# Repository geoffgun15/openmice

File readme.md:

# OpenMice

Custom PAW3395 rechargeable mouse, USB wireless receiver, and browser configurator.

Standalone repository: https://github.com/geoffgun15/openmice.
Migrated from the original fork with all eight commits retained and the
confidential PixArt PDF removed from every commit. Historical commit IDs changed.

**A1 is a routed prototype package.** Both boards pass KiCad electrical,
clearance, connectivity and schematic parity checks. Custom runtime and
bootloader builds, factory HEX, runtime UF2 and fabrication exports are included.
**Physical tests are NOT RUN: there is no assembled board.** Review the
[first-article procedure](docs/FIRST_ARTICLE.md) and
[fabrication requirements](docs/FABRICATION.md) before a prototype order.

| Component | Included |
|---|---|
| Mouse | Bare PAW3395, nRF52840 module, 1S LiPo charger/power path, five buttons + scroll |
| Receiver | Custom nRF52840 board, USB-C, BLE-to-USB HID and configuration bridge |
| Firmware | Corrected sensor startup/ID/timing, 16-bit motion, DPI, bindings, persistence |
| Editor | Web Serial, DPI, mouse/keyboard bindings, Apply/Save, import/export and demo |

The radio modules are soldered components on custom PCBs; nice!nano is no longer
used. BLE is the prototype radio; proprietary 1000 Hz wireless is not implemented.

- [Hardware files and validation status](hardware/README.md)
- [Setup, protocol and verification](docs/SETUP.md)
- [Mouse schematic](hardware/mouse/mouse.kicad_sch) / [PCB](hardware/mouse/mouse.kicad_pcb)
- [Receiver schematic](hardware/receiver/receiver.kicad_sch) / [PCB](hardware/receiver/receiver.kicad_pcb)
- [Browser editor](web/index.html)

## Board renders

KiCad assembly renders with all 51 mouse and 18 receiver components fitted.
The sensor, radio module, USB-C, charger and crystal use simplified visual models;
these images do not validate mechanical fit. The battery, main click switches
and scroll encoder connect externally. See [model details](hardware/libraries/3dmodels/README.md).

| Mouse PCB · 64 × 94 mm | Wireless receiver PCB · 28 × 54 mm |
|---|---|
|  |  |

Bare PCB views: [mouse](output/hardware/mouse/board-3d.png) ·
[receiver](output/hardware/receiver/board-3d.png).

## Preview

```sh
python -m http.server 8765 --bind 127.0.0.1 --directory web
```

Open http://127.0.0.1:8765/ in desktop Chrome/Edge. Demo mode works without hardware.
A real connection requires the supplied runtime and mouse/receiver.

Native build details, hashes and CAD export workflow: [BUILD.md](docs/BUILD.md).

## Development

```sh
python -m unittest discover -s tests -v
node --test web/test.mjs
python tools/package_firmware.py
```

`tools/build_hardware.py` regenerates starting placements and overwrites manual edits.
The confidential sensor PDF is excluded from this public repository and its Git history.
Prototype assumptions: LM19-LSI optics,
64 x 94 mm mouse outline, external switch/encoder contacts, and a protected
300 mAh cell with compatible NTC temperature sensing.

Project code: MIT. Vendored KiCad libraries retain their upstream licenses;
see hardware/README.md. Obtain sensor documentation through an authorized source.

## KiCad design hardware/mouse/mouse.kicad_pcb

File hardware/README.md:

# Hardware A1: routed prototype candidates

Both custom boards are routed and have zero findings in KiCad 10.0.6 ERC,
DRC, connectivity and schematic parity checks. Manufacturing exports are in
`output/hardware/` and fabrication ZIPs in `output/`. **Physical tests are NOT RUN.**

| Board | Outline | Components | Functional nets |
|---|---|---:|---:|
| Mouse | 64 × 94 mm | 51 | 39 |
| USB-C receiver | 28 × 54 mm | 18 | 13 |

Both boards use soldered Raytac MDBT50Q-1MV2 nRF52840 modules. The mouse has a
bare PAW3395DM-T6QU, 1.9 V sensor/LED rail, 3.0 V MCU/VDDIO rail, external contact
headers for five switches and a scroll encoder, USB-C, SWD and Pair/reset buttons.
The receiver connects by USB-C cable and bridges BLE input/configuration to USB.
Proprietary 1000 Hz wireless is not implemented.

BQ24072 provides charging and system power path for a protected 1S 3.7 V nominal
300 mAh LiPo pack with thermally attached compatible 10k NTC (J3 BAT+, GND, NTC).
USB100 mode caps total input at 100 mA; R_ISET 5.90k programs about 151 mA before
input/system limits, R_ILIM 3.09k is overridden, R_TMR 68k is about 9.1 hours nominal.
The switch is downstream of charging. Firmware battery telemetry is approximate;
pack protection handles over-discharge. USB suspend management is not implemented.

Sensor VDDREG is decoupled only. TLV70019 supplies sensor VDD/LED (5.6 ohm 1%
resistor); TLV70030 supplies VDDIO and MCU VDD/VDDH. DCCH is unconnected. Separate
5.1k CC resistors and USBLC6-2SC6 protect USB; no PD. External 32.768 kHz crystal
loading needs bench verification. The module includes its normal-mode DC/DC parts.

Four layers use outer signal routing and two solid inner GND reference planes,
all-layer antenna keep-outs, routed optical/mounting apertures and charger thermal
vias. USB routing is manually protected. Review the
[fabrication specification](../docs/FABRICATION.md) for stack-up, impedance, filled thermal vias, lens and BOM
requirements before a first-article order. No shell or optical fit validation exists.

Editable native schematics/boards, local libraries, routing DSN/SES, BOM, placement
CSV and CAD-check reports are included. Regeneration overwrites routing; see
[build workflow](../docs/BUILD.md). The unused MouseSwitch_D2F_DRAFT footprint is
not in either BOM and is not validated. Bench bring-up is in
[FIRST_ARTICLE.md](../docs/FIRST_ARTICLE.md).

## References and licenses

- PAW3395DM-T6QU datasheet v1.3 (8 Apr 2024): confidential reference, excluded
  from this public repository; obtain through an authorized source.
- [Raytac module datasheet](https://www.raytac.com/tw/download/index.php?index_id=24).
- [BQ2407x datasheet, including BQ24072](https://www.ti.com/lit/ds/symlink/bq24074.pdf).
- [TLV700 regulators](https://www.ti.com/product/TLV700).
- [KiCad footprints](https://github.com/KiCad/kicad-footprints) and
  [symbols](https://github.com/KiCad/kicad-symbols).

Vendored KiCad data retains upstream CC-BY-SA 4.0 licensing with the KiCad library
exception; see the [library license](https://www.kicad.org/libraries/license/).
Project code uses MIT. The confidential PixArt reference is not distributed.

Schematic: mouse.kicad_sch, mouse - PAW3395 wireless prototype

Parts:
C1, C5, C8: 1uF 10V X7R; C_0603_1608Metric
C2: 4.7uF 6.3V X5R; C_0603_1608Metric
C3, C4: 100nF 10V X7R; C_0603_1608Metric
C6, C7: 18pF C0G (tune); C_0603_1608Metric
C9, C17, C18: 10uF 6.3V X5R; C_0805_2012Metric
C10, C12, C14, C19: 100nF X7R; C_0603_1608Metric
C11: 4.7uF X5R; C_0603_1608Metric
C13: 10uF X5R; C_0805_2012Metric
C15: 33uF 6.3V X5R; C_0805_2012Metric
C16: 1uF 10V X7R; C_0805_2012Metric
J1: USB-C HRO TYPE-C-31-M-12; USB_C
J2: SWD: VDD / SWDIO / SWDCLK / GND / RESET; PinHeader_1x05_P2.54mm_Vertical
J3: Protected 1S 300mAh + 10k NTC (BAT/GND/NTC); JST_PH_B3B-PH-K_1x03_P2.00mm_Vertical
J4: Charger status: GND / PGOOD / CHG; PinHeader_1x03_P2.54mm_Vertical
J5: BUTTON_LEFT contact; PinHeader_1x02_P2.54mm_Vertical
J6: BUTTON_RIGHT contact; PinHeader_1x02_P2.54mm_Vertical
J7: BUTTON_MIDDLE contact; PinHeader_1x02_P2.54mm_Vertical
J8: BUTTON_BACK contact; PinHeader_1x02_P2.54mm_Vertical
J9: BUTTON_FORWARD contact; PinHeader_1x02_P2.54mm_Vertical
J10: Encoder: A / GND / B; PinHeader_1x03_P2.54mm_Vertical
R1, R2: 5.1k 1%; R_0603_1608Metric
R3, R5: 10k; R_0603_1608Metric
R4: 5.6R 1%; R_0603_1608Metric
R6: 5.90k 1%; R_0603_1608Metric
R7: 3.09k 1%; R_0603_1608Metric
R8: 68k 1%; R_0603_1608Metric
R9, R10: 100k 1%; R_0603_1608Metric
R11, R12: 100k; R_0603_1608Metric
SW1: PAIR TL3342; SW_SPST_TL3342
SW2: RESET TL3342; SW_SPST_TL3342
SW3: Power PCM12; SW_SPDT_PCM12
U1: MDBT50Q-1MV2; Raytac_MDBT50Q
U2: USBLC6-2SC6; SOT-23-6
U3: TLV70030DDCR; SOT-23-5
U4: PAW3395DM-T6QU; PAW3395DM_T6QU
U5: TLV70019DDCR; SOT-23-5
U6: BQ24072RGTR; BQ24072_RGT0016C
Y1: 32.768kHz 12.5pF ABS07; Crystal_SMD_3215-2Pin_3.2x1.5mm

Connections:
/BATTERY: C18.1, J3.1, R9.1, U6.2 (BAT), U6.3 (BAT)
/BATTERY_ADC: C19.1, R9.2, R10.1, U1.20 (P0.04/AIN2)
/BATTERY_NTC: J3.3, U6.1 (TS)
/BUTTON_BACK: J8.1, U1.46 (P0.22)
/BUTTON_FORWARD: J9.1, U1.48 (P0.24)
/BUTTON_LEFT: J5.1, U1.44 (P0.20)
/BUTTON_MIDDLE: J7.1, U1.45 (P0.23)
/BUTTON_RIGHT: J6.1, U1.43 (P0.21)
/CC1: J1.A5, R1.1
/CC2: J1.B5, R2.1
/CHARGER_ILIM: R7.1, U6.12 (ILIM)
/CHARGER_ISET: R6.1, U6.16 (ISET)
/CHARGER_TMR: R8.1, U6.14 (TMR)
/CHARGING: J4.3, R12.2, U6.9 (CHG)
/ENCODER_A: J10.1, U1.49 (P0.25)
/ENCODER_B: J10.3, U1.19 (P0.26)
/GND: C1.2, C2.2, C3.2, C4.2, C5.2, C6.2, C7.2, C8.2, C9.2, C10.2, C11.2, C12.2, C13.2, C14.2, C15.2, C16.2, C17.2, C18.2, C19.2, J1.A1, J1.A12, J1.B1, J1.B12, J1.S1, J2.4, J3.2, J4.1, J5.2, J6.2, J7.2, J8.2, J9.2, J10.2, R1.2, R2.2, R6.2, R7.2, R8.2, R10.2, SW1.2, SW2.2, U1.1 (GND), U1.2 (GND), U1.15 (GND), U1.33 (GND), U1.55 (GND), U2.2, U3.2, U4.3 (GND), U4.8 (GNDIO), U5.2, U6.4 (CE), U6.5 (EN2), U6.6 (EN1), U6.8 (VSS), U6.15 (TD), U6.17 (EP)
/LF_XL1: C6.1, U1.17 (XL1/P0.00), Y1.1
/LF_XL2: C7.1, U1.18 (XL2/P0.01), Y1.2
/MCU_RESET: J2.5, R3.2, SW2.1, U1.40 (~RESET~/P0.18)
/PAIR: SW1.1, U1.16 (P0.27)
/POWER_GOOD: J4.2, R11.2, U6.7 (PGOOD)
/SENSOR_IRQ: U1.27 (TRACEDATA2/P0.11), U4.9 (MOTION)
/SENSOR_LED_P: R4.2, U4.15 (LED_P)
/SENSOR_NCS: U1.38 (P0.16), U4.13 (NCS)
/SENSOR_RESET: U1.41 (P0.17), U4.14 (NRESET)
/SENSOR_VDDREG: C11.1, C12.1, U4.5 (VDDREG)
/SPI_MISO: R5.2, U1.39 (P0.15), U4.12 (MISO)
/SPI_MOSI: U1.37 (P0.13), U4.11 (MOSI)
/SPI_SCLK: U1.36 (P0.14), U4.10 (SCLK)
/SWDCLK: J2.3, U1.53 (SWDCLK)
/SWDIO: J2.2, U1.51 (SWDIO)
/SYSTEM: C17.1, SW3.1, U6.10 (OUT), U6.11 (OUT)
/SYSTEM_ON: C1.1, SW3.2, U3.1, U3.3
/USB_DM: J1.A7, J1.B7, U1.34 (D-), U2.3, U2.4
/USB_DP: J1.A6, J1.B6, U1.35 (D+), U2.1, U2.6
/USB_VBUS: C5.1, C16.1, J1.A4, J1.A9, J1.B4, J1.B9, U1.32 (VBUS), U2.5, U6.13 (IN)
/VDD_1V9: C9.1, C10.1, C15.1, R4.1, U4.4 (VDD), U5.5
/VDD_3V0: C2.1, C3.1, C4.1, C8.1, C13.1, C14.1, J2.1, R3.1, R5.1, R11.1, R12.1, U1.28 (VDD), U1.30 (VDDH), U3.5, U4.7 (VDDIO), U5.1, U5.3

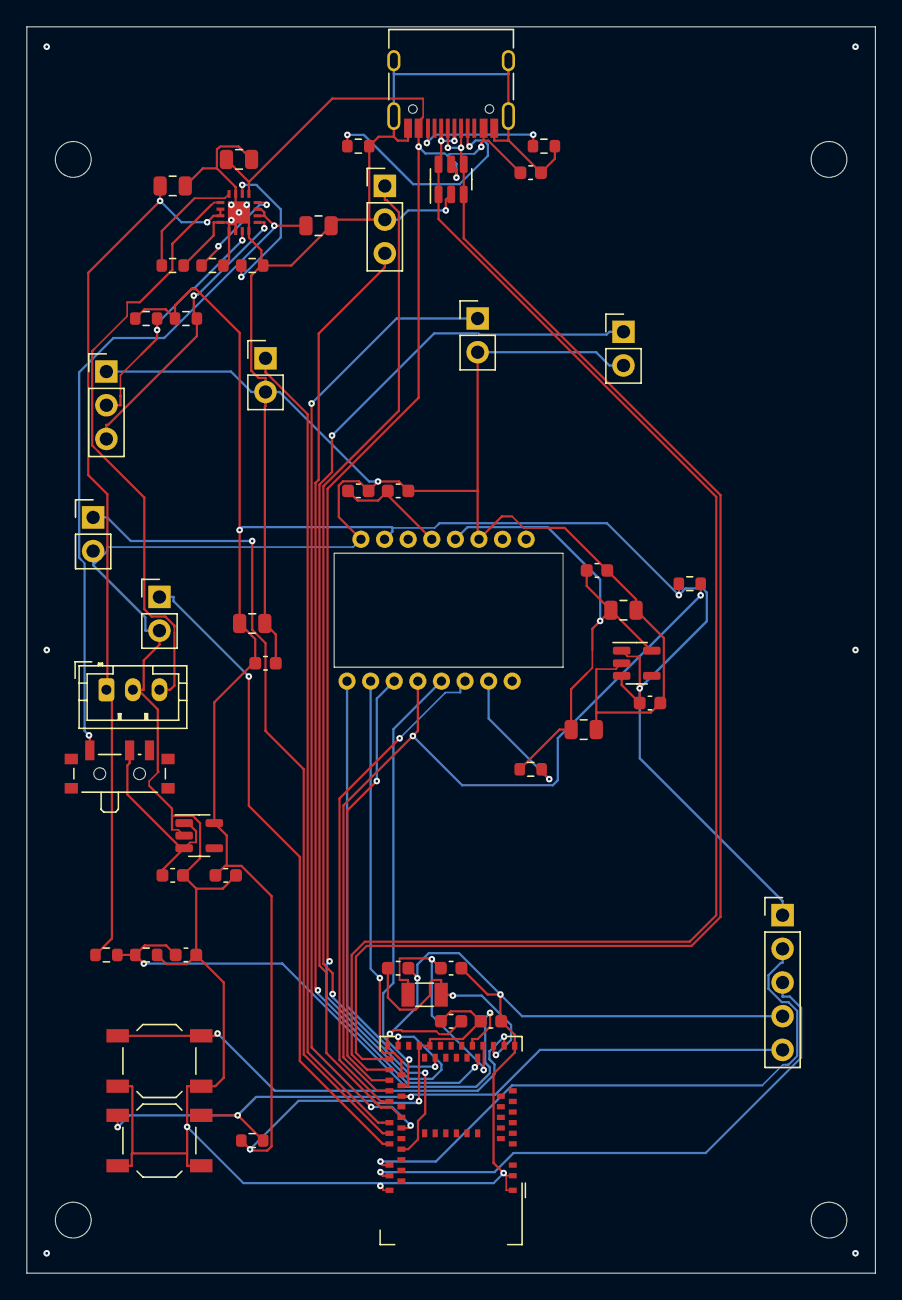
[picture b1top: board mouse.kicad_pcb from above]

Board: 4 copper layers, 64.0 x 94.0 mm, 51 parts (0 on the bottom side), 39 nets.

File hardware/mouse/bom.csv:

Reference,Value / part,Footprint,X mm,Y mm,Block
U1,MDBT50Q-1MV2,Raytac_MDBT50Q,32,84,controller
J1,USB-C HRO TYPE-C-31-M-12,USB_C,32,3.6,USB
U2,USBLC6-2SC6,SOT-23-6,38,7.6,USB
R1,5.1k 1%,R_0603_1608Metric,26,7.6,USB
R2,5.1k 1%,R_0603_1608Metric,29,7.6,USB
U3,TLV70030DDCR,SOT-23-5,13,61,power
C1,1uF 10V X7R,C_0603_1608Metric,11,64,power
C2,4.7uF 6.3V X5R,C_0603_1608Metric,15,64,power
C3,100nF 10V X7R,C_0603_1608Metric,32,75,controller
C4,100nF 10V X7R,C_0603_1608Metric,35,75,controller
C5,1uF 10V X7R,C_0603_1608Metric,35,10.6,USB
Y1,32.768kHz 12.5pF ABS07,Crystal_SMD_3215-2Pin_3.2x1.5mm,30,73,controller
C6,18pF C0G (tune),C_0603_1608Metric,28,71,controller
C7,18pF C0G (tune),C_0603_1608Metric,32,71,controller
J2,SWD: VDD / SWDIO / SWDCLK / GND / RESET,PinHeader_1x05_P2.54mm_Vertical,57,67,debug
SW1,PAIR TL3342,SW_SPST_TL3342,10,78,controls
SW2,RESET TL3342,SW_SPST_TL3342,10,84,controls
R3,10k,R_0603_1608Metric,14,84,controller
U4,PAW3395DM-T6QU,PAW3395DM_T6QU,32,44,sensor
U5,TLV70019DDCR,SOT-23-5,46,48,sensor
C8,1uF 10V X7R,C_0603_1608Metric,47,51,sensor
C9,10uF 6.3V X5R,C_0805_2012Metric,45,44,sensor
C10,100nF X7R,C_0603_1608Metric,43,41,sensor
C11,4.7uF X5R,C_0603_1608Metric,25,35,sensor
C12,100nF X7R,C_0603_1608Metric,28,35,sensor
C13,10uF X5R,C_0805_2012Metric,17,45,sensor
C14,100nF X7R,C_0603_1608Metric,18,48,sensor
C15,33uF 6.3V X5R,C_0805_2012Metric,42,53,sensor
R4,5.6R 1%,R_0603_1608Metric,40,52,sensor
R5,10k,R_0603_1608Metric,50,42,sensor
U6,BQ24072RGTR,VQFN-16-1EP_3x3mm_P0.5mm_EP1.45x1.45mm,16,14,battery
J3,Protected 1S 300mAh + 10k NTC (BAT/GND/NTC),JST_PH_B3B-PH-K_1x03_P2.00mm_Vertical,6,53,battery
R6,5.90k 1%,R_0603_1608Metric,11,18,battery
R7,3.09k 1%,R_0603_1608Metric,14,18,battery
R8,68k 1%,R_0603_1608Metric,17,18,battery
C16,1uF 10V X7R,C_0805_2012Metric,16,10,battery
C17,10uF 6.3V X5R,C_0805_2012Metric,20,17,battery
C18,10uF 6.3V X5R,C_0805_2012Metric,11,12,battery
SW3,Power PCM12,SW_SPDT_PCM12,7,63,battery
R9,100k 1%,R_0603_1608Metric,6,70,battery
R10,100k 1%,R_0603_1608Metric,9,70,battery
C19,100nF X7R,C_0603_1608Metric,12,70,battery
R11,100k,R_0603_1608Metric,9,22,battery
R12,100k,R_0603_1608Metric,12,22,battery
J4,Charger status: GND / PGOOD / CHG,PinHeader_1x03_P2.54mm_Vertical,6,26,battery
J5,BUTTON_LEFT contact,PinHeader_1x02_P2.54mm_Vertical,18,25,controls
J6,BUTTON_RIGHT contact,PinHeader_1x02_P2.54mm_Vertical,44,25,controls
J7,BUTTON_MIDDLE contact,PinHeader_1x02_P2.54mm_Vertical,30,20,controls
J8,BUTTON_BACK contact,PinHeader_1x02_P2.54mm_Vertical,5,39,controls
J9,BUTTON_FORWARD contact,PinHeader_1x02_P2.54mm_Vertical,5,44,controls
J10,Encoder: A / GND / B,PinHeader_1x03_P2.54mm_Vertical,27,12,controls

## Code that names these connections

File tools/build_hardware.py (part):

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        parts.append(value)
        return value
    mx,my = (14,44) if receiver else (32,84)
    gpio = {27:'SENSOR_IRQ',36:'SPI_SCLK',37:'SPI_MOSI',38:'SENSOR_NCS',39:'SPI_MISO',41:'SENSOR_RESET',43:'BUTTON_RIGHT',44:'BUTTON_LEFT',45:'BUTTON_MIDDLE',46:'BUTTON_BACK',48:'BUTTON_FORWARD',49:'ENCODER_A',19:'ENCODER_B',20:'BATTERY_ADC'}
    module_nets = {1:'GND',2:'GND',15:'GND',28:'VDD_3V0',30:'VDD_3V0',32:'USB_VBUS',33:'GND',34:'USB_DM',35:'USB_DP',40:'MCU_RESET',51:'SWDIO',53:'SWDCLK',55:'GND',16:'PAIR',17:'LF_XL1',18:'LF_XL2'}
    if not receiver:
        module_nets.update(gpio)
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    for i,(dx,dy) in enumerate(((0,-9),(3,-9))):
        add('C'+str(3+i),'100nF 10V X7R','C_0603_1608Metric',mx+dx,my+dy,{1:'VDD_3V0',2:'GND'},group='controller')
    add('C5','1uF 10V X7R','C_0603_1608Metric',ux+6,11,{1:'USB_VBUS',2:'GND'},group='USB')
    add('Y1','32.768kHz 12.5pF ABS07','Crystal_SMD_3215-2Pin_3.2x1.5mm',mx-2,my-11,{1:'LF_XL1',2:'LF_XL2'},group='controller')
    for i,net in enumerate(('LF_XL1','LF_XL2')):
        add('C'+str(6+i),'18pF C0G (tune)','C_0603_1608Metric',mx-4+i*4,my-13,{1:net,2:'GND'},group='controller')
    add('J2','SWD: VDD / SWDIO / SWDCLK / GND / RESET','PinHeader_1x05_P2.54mm_Vertical',2.8 if receiver else 57,28 if receiver else 67,{1:'VDD_3V0',2:'SWDIO',3:'SWDCLK',4:'GND',5:'MCU_RESET'},group='debug')
    add('SW1','PAIR TL3342','SW_SPST_TL3342',5 if receiver else 10,15 if receiver else 78,{1:'PAIR',2:'GND'},group='controls')
    add('SW2','RESET TL3342','SW_SPST_TL3342',23 if receiver else 10,27 if receiver else 84,{1:'MCU_RESET',2:'GND'},group='controls')
    add('R3','10k','R_0603_1608Metric',23 if receiver else 17,33 if receiver else 84,{1:'VDD_3V0',2:'MCU_RESET'},group='controller')
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    add('C19','100nF X7R','C_0603_1608Metric',12,70,{1:'BATTERY_ADC',2:'GND'},group='battery')
    for ref,net,x in [('R11','POWER_GOOD',9),('R12','CHARGING',12)]:
        add(ref,'100k','R_0603_1608Metric',x,22,{1:'VDD_3V0',2:net},group='battery')
    add('J4','Charger status: GND / PGOOD / CHG','PinHeader_1x03_P2.54mm_Vertical',6,26,{1:'GND',2:'POWER_GOOD',3:'CHARGING'},group='battery')
    # External contacts allow the first prototype to fit a future shell.
    for i,(net,x,y) in enumerate([('BUTTON_LEFT',18,25),('BUTTON_RIGHT',45,23),('BUTTON_MIDDLE',34,22),('BUTTON_BACK',5,37),('BUTTON_FORWARD',10,43)]):
        add('J'+str(5+i),net+' contact','PinHeader_1x02_P2.54mm_Vertical',x,y,{1:net,2:'GND'},group='controls')
    add('J10','Encoder: A / GND / B','PinHeader_1x03_P2.54mm_Vertical',27,12,{1:'ENCODER_A',2:'GND',3:'ENCODER_B'},group='controls')
    return parts

def make_schematic(name,parts):
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    assert all(len(nodes)>=2 for net,nodes in nets.items()),[(net,nodes) for net,nodes in nets.items() if len(nodes)<2]
    print(name,len(parts),'components,',len(nets),'connected nets; structure checked')

(HW/'pin-map.json').write_text(json.dumps({'SCLK':'P0_14','MOSI':'P0_13','MISO':'P0_15','NCS':'P0_16','SENSOR_RESET':'P0_17','MOTION':'P0_11','BUTTONS':['P0_20','P0_21','P0_23','P0_22','P0_24'],'ENCODER':['P0_25','P0_26'],'PAIR':'P0_27','BATTERY_ADC':'P0_04','MCU_RESET':'P0_18'},indent=2)+'\n')

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
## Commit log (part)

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2025-04-29 init commit
2025-04-29 added a new fw file
2025-04-29 added readme
